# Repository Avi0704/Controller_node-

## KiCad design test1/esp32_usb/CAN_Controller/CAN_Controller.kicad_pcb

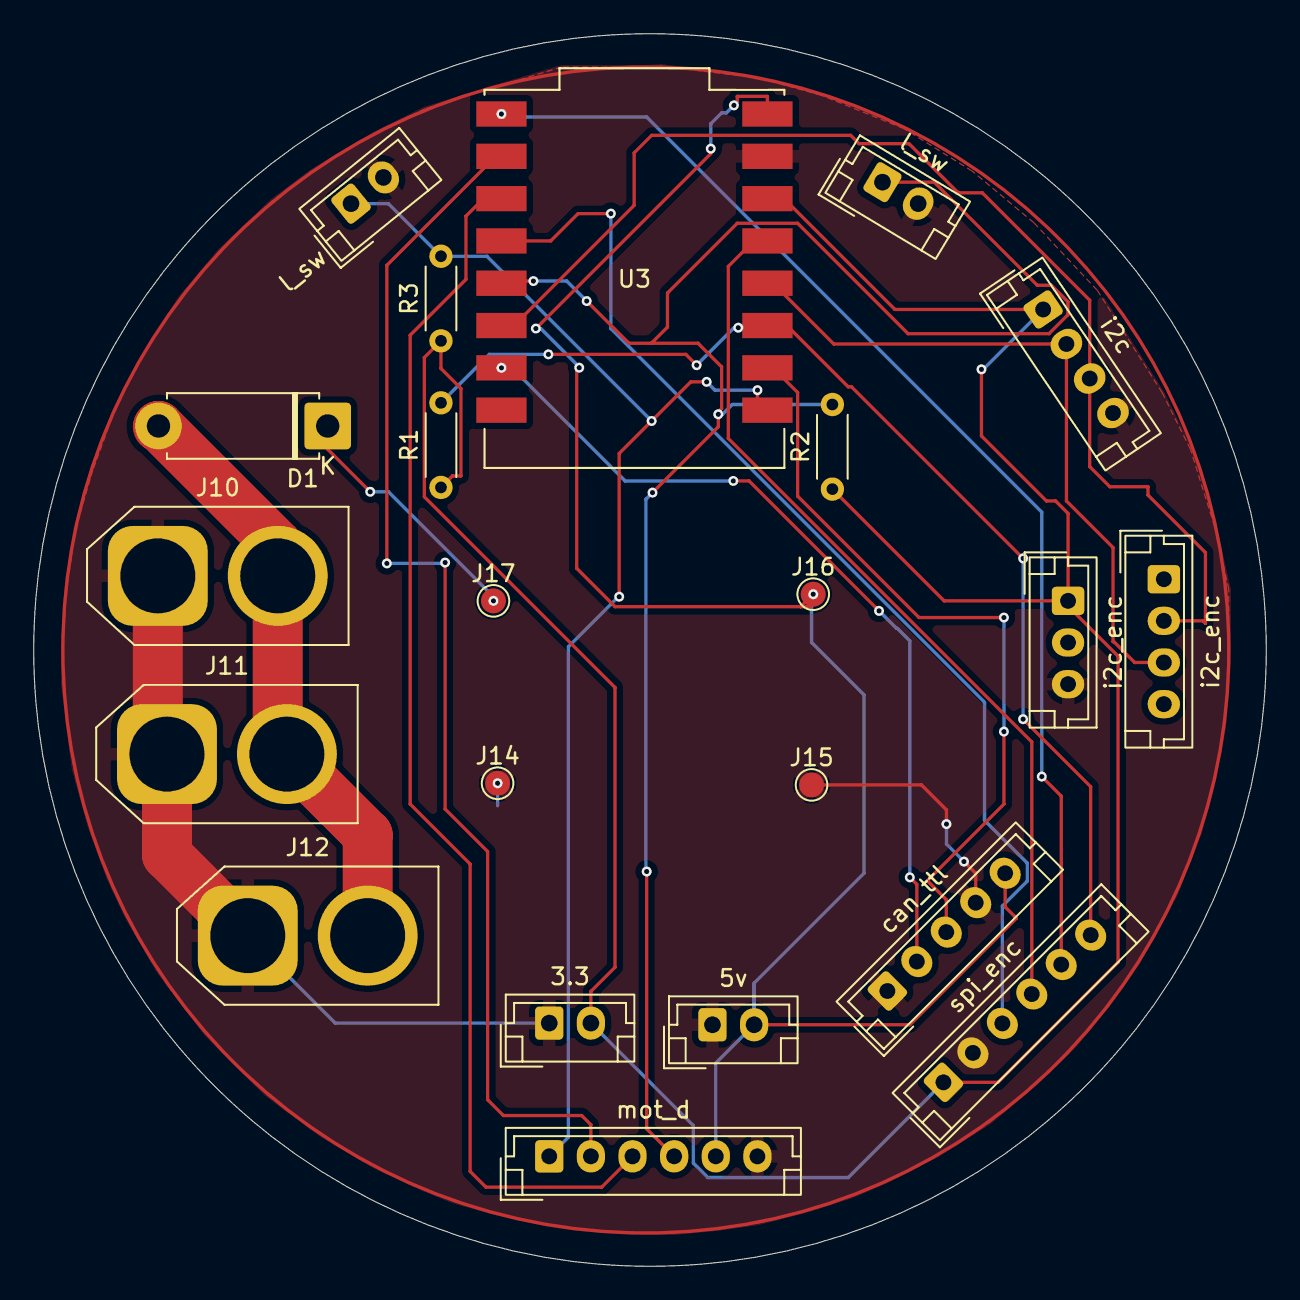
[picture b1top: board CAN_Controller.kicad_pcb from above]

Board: 2 copper layers, 74.0 x 74.0 mm, 22 parts (0 on the bottom side), 17 nets.

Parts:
3.3, 5v: Power; JST_EH_B2B-EH-A_1x02_P2.50mm_Vertical
D1: D; D_5W_P10.16mm_Horizontal
J10, J11, J12: XT_60; AMASS_XT60-M_1x02_P7.20mm_Vertical
J14, J15, J16, J17: SO09; TestPoint_Pad_D1.5mm
R1, R2, R3: 10k; R_Axial_DIN0204_L3.6mm_D1.6mm_P5.08mm_Horizontal
U3: ESP32-C3_SUPERMINI_SMD; MODULE_ESP32-C3_SUPERMINI
can_ttl: CAN_TTL_CONV; JST_EH_B5B-EH-A_1x05_P2.50mm_Vertical
i2c: I2C BUS; JST_EH_B4B-EH-A_1x04_P2.50mm_Vertical
i2c_enc: AS5600_I2C; JST_EH_B4B-EH-A_1x04_P2.50mm_Vertical
i2c_enc#2: As5600_3pins; JST_EH_B3B-EH-A_1x03_P2.50mm_Vertical
l_sw: Optional_SW; JST_EH_B2B-EH-A_1x02_P2.50mm_Vertical
l_sw#2: Optional_SW; JST_EH_B2B-EH-A_1x02_P2.50mm_Vertical
mot_d: BTS7960j; JST_EH_B6B-EH-A_1x06_P2.50mm_Vertical
spi_enc: MT6835; JST_EH_B6B-EH-A_1x06_P2.50mm_Vertical

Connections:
+3.3V: 3.3.2, R1.1, R2.1, R3.1, U3.3.3 (3V3), i2c.1, i2c_enc#2.1, spi_enc.1
+5V: 5v.2, J16.1 (Pin_1_1), U3.5V, can_ttl.5, mot_d.5
CAN_RXD: U3.20 (GPIO20), can_ttl.2
CAN_TXD: U3.1 (GPIO1), can_ttl.3
CSN: R1.2, U3.2 (GPIO2), spi_enc.6
EN_L: R2.2, U3.9 (GPIO9), l_sw.1, mot_d.4
EN_R: R3.2, U3.0 (GPIO0), l_sw#2.1, mot_d.1
GND: 3.3.1, 5v.1, J10.1, J11.1, J12.1, J14.1 (Pin_1_1), J15.1 (Pin_1_1), U3.G (GND), can_ttl.1, can_ttl.4, i2c.4, i2c_enc#2.3, l_sw.2, l_sw#2.2, mot_d.6, spi_enc.2
MISO: U3.4 (GPIO4), spi_enc.4
MOSI: U3.5 (GPIO5), spi_enc.5
unnamed: D1.2 (A), J10.2, J11.2, J12.2
PWM_L: U3.7 (GPIO7), mot_d.3
PWM_R: U3.6 (GPIO6), mot_d.2
SCK: U3.8 (GPIO8), spi_enc.3
SCL: U3.10 (GPIO10), i2c.3, i2c_enc.2
SDA: U3.3 (GPIO3), i2c.2, i2c_enc.3
VAA: D1.1 (K), J17.1 (Pin_1_1)
